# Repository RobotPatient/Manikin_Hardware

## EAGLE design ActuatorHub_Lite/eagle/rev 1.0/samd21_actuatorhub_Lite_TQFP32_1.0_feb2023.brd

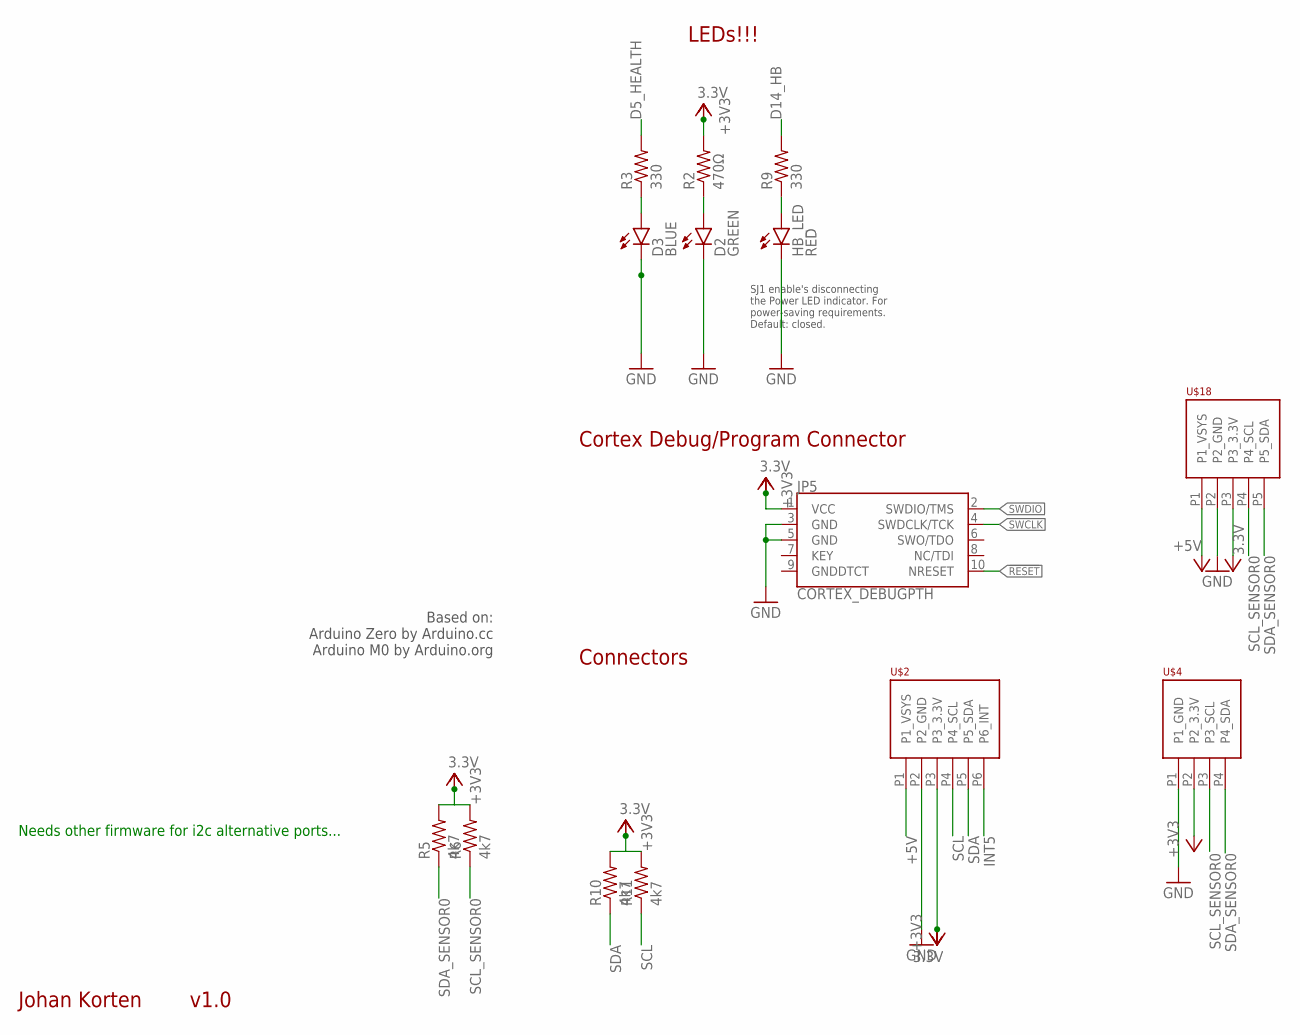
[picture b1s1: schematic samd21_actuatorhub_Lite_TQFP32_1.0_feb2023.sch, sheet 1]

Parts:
D2: GREEN; LED-0603
D3: BLUE; LED-0603
HB_LED: RED; LED-0603
JP5: CORTEX_DEBUGPTH; 2X5-PTH-1.27MM
R2: 470Ω; 0603-RES
R3, R9: 330; 0603-RES
R5, R6, R10, R11: 4k7; 0603-RES
U$2: PHOENIX_PTSM_M6_TH_I2CPPANGLE; PTSM_M6_THRHOLE
U$4: PHOENIX_PTSM_M4_THANGLE; PTSM_M4_TH
U$18: PHOENIX_PTSM_M5_TH_I2C++; PTSM_M5_THRHOLE

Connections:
3.3V: JP5.1 (VCC), R2.2, R5.2, R6.2, R10.2, R11.2, U$2.P3 (P3_3.3V), U$4.P2 (P2_3.3V), U$18.P3 (P3_3.3V); also elsewhere on the board
!RESET: JP5.10 (NRESET); also elsewhere on the board
+5V: U$2.P1 (P1_VSYS), U$18.P1 (P1_VSYS); also elsewhere on the board
D5_HEALTH: R3.2; also elsewhere on the board
D5_HEALTH_LED: D3.A, R3.1
D14_HB: R9.2; also elsewhere on the board
D14_HB_LED: HB_LED.A, R9.1
GND: D2.C, D3.C, HB_LED.C, JP5.3 (GND), JP5.5 (GND), U$2.P2 (P2_GND), U$4.P1 (P1_GND), U$18.P2 (P2_GND); also elsewhere on the board
INT5: U$2.P6 (P6_INT); also elsewhere on the board
unnamed: D2.A, R2.1
SCL: R11.1, U$2.P4 (P4_SCL); also elsewhere on the board
SCL_SENSOR0: R6.1, U$4.P3 (P3_SCL), U$18.P4 (P4_SCL); also elsewhere on the board
SDA: R10.1, U$2.P5 (P5_SDA); also elsewhere on the board
SDA_SENSOR0: R5.1, U$4.P4 (P4_SDA), U$18.P5 (P5_SDA); also elsewhere on the board
SWCLK: JP5.4 (SWDCLK/TCK); also elsewhere on the board
SWDIO: JP5.2 (SWDIO/TMS); also elsewhere on the board

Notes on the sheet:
LEDs!!!
Cortex Debug/Program Connector
Connectors
Johan Korten
v1.0
SJ1 enable's disconnecting the Power LED indicator. For power-saving requirements. Default: closed.
Based on: Arduino Zero by Arduino.cc Arduino M0 by Arduino.org
Needs other firmware for i2c alternative ports...

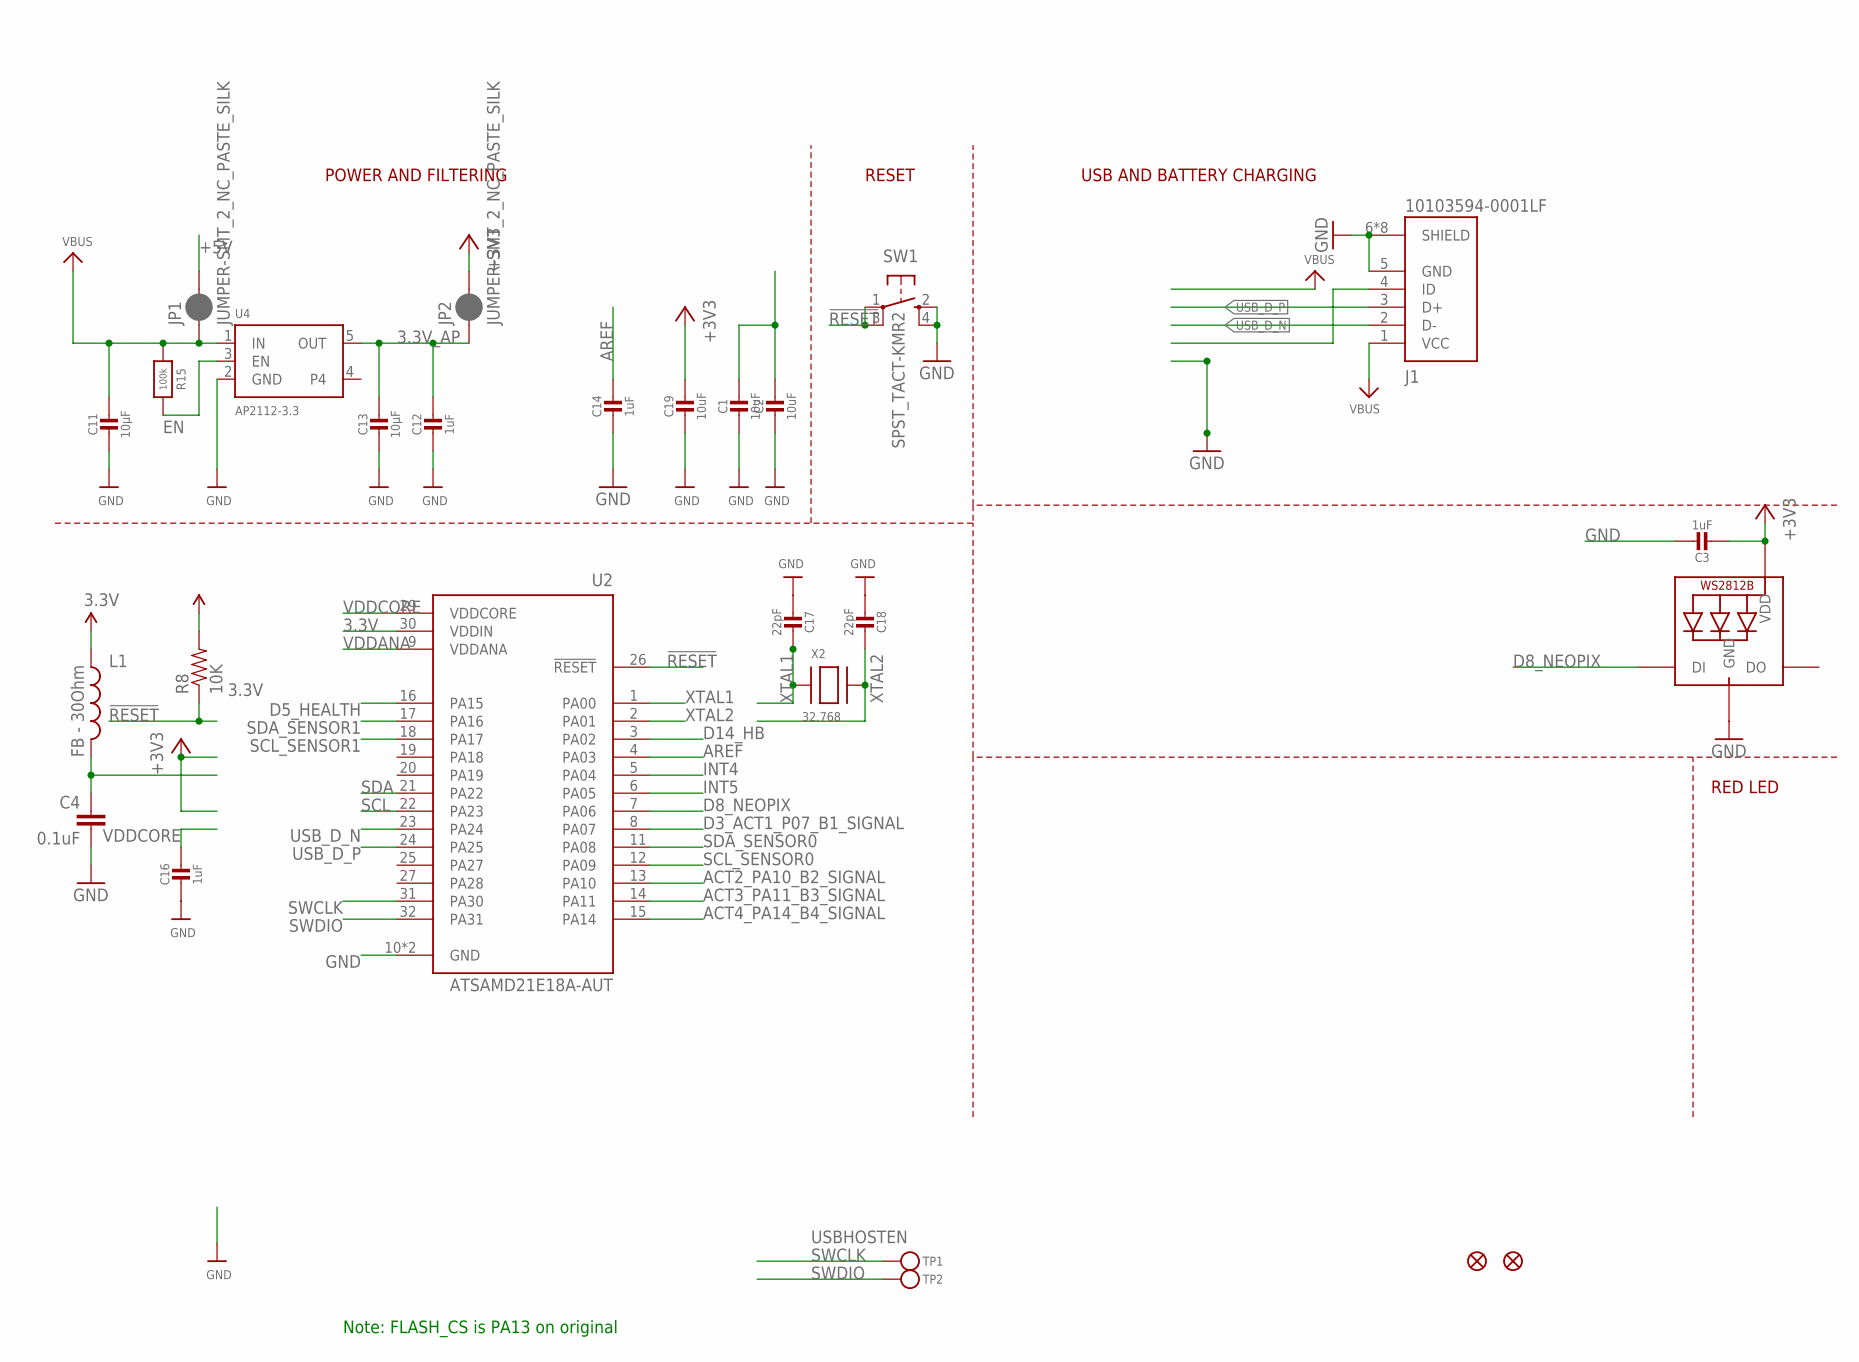
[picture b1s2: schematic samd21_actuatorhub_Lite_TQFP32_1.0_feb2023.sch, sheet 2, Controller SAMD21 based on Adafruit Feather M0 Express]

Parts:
C1, C2, C19: 10uF; 0805-NO
C3, C12, C14, C16: 1uF; 0603-NO
C4: 0.1uF; 0402-CAP
C11, C13: 10µF; 0805-NO
C17, C18: 22pF; 0603-NO
J1: 10103594-0001LF; AMPHENOL_10103594-0001LF
JP1, JP2: JUMPER-SMT_2_NC_PASTE_SILK; SMT-JUMPER_2_NC_PASTE_SILK
L1: FB - 30Ohm; 0603
LED1: WS2812B3535; LED3535
R8: 10K; 0603-RES
R15: 100k; 0603-NO
SW1: SPST_TACT-KMR2; KMR2
TP1, TP2: TESTPOINTROUND1.5MM; TESTPOINT_ROUND_1.5MM
U2: ATSAMD21E18A-AUT; QFP80P900X900X120-32N
U4: AP2112-3.3; SOT23-5
U$34, U$35: FIDUCIAL""; FIDUCIAL_1MM
X2: 32.768; XTAL3215

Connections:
3.3V: C3.2, C19.1, JP2.2, L1.1, LED1.2 (VDD), R8.2, U2.30 (VDDIN); also elsewhere on the board
3.3V_AP: C12.1, C13.1, JP2.1, U4.5 (OUT)
!RESET: R8.1, SW1.1, SW1.3 (P1), U2.26 (!RESET); also elsewhere on the board
+5V: C1.1, C2.1, JP1.2; also elsewhere on the board
ACT2_PA10_B2_SIGNAL: U2.13 (PA10); also elsewhere on the board
ACT3_PA11_B3_SIGNAL: U2.14 (PA11); also elsewhere on the board
ACT4_PA14_B4_SIGNAL: U2.15 (PA14); also elsewhere on the board
AREF: C14.1, U2.4 (PA03)
D3_ACT1_P07_B1_SIGNAL: U2.8 (PA07); also elsewhere on the board
D5_HEALTH: U2.16 (PA15); also elsewhere on the board
D8_NEOPIX: LED1.1 (DI), U2.7 (PA06)
D14_HB: U2.3 (PA02); also elsewhere on the board
EN: R15.2, U4.3 (EN)
GND: C1.2, C2.2, C3.1, C4.2, C11.2, C12.2, C13.2, C14.2, C16.2, C17.2, C18.2, C19.2, J1.5 (GND), J1.6 (SHIELD), J1.7 (SHIELD), J1.8 (SHIELD), J1.9 (SHIELD), J1.10 (SHIELD), J1.11 (SHIELD), J1.S1 (SHIELD), J1.S2 (SHIELD), LED1.4 (GND), SW1.2 (S), SW1.4 (S1), U2.10 (GND), U2.28 (GND), U4.2 (GND); also elsewhere on the board
INT4: U2.5 (PA04)
INT5: U2.6 (PA05); also elsewhere on the board
SCL: U2.22 (PA23); also elsewhere on the board
SCL_SENSOR0: U2.12 (PA09); also elsewhere on the board
SCL_SENSOR1: U2.18 (PA17)
SDA: U2.21 (PA22); also elsewhere on the board
SDA_SENSOR0: U2.11 (PA08); also elsewhere on the board
SDA_SENSOR1: U2.17 (PA16)
SWCLK: TP1.P$1, U2.31 (PA30); also elsewhere on the board
SWDIO: TP2.P$1, U2.32 (PA31); also elsewhere on the board
USB_D_N: J1.2 (D-), U2.23 (PA24)
USB_D_P: J1.3 (D+), U2.24 (PA25)
VBUS: C11.1, J1.1 (VCC), JP1.1, R15.1, U4.1 (IN)
VDDANA: C4.1, L1.2, U2.9 (VDDANA)
VDDCORE: C16.1, U2.29 (VDDCORE)
XTAL1: C17.1, U2.1 (PA00), X2.P$1
XTAL2: C18.1, U2.2 (PA01), X2.P$2

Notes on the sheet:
POWER AND FILTERING
RESET
USBHOSTEN
USB AND BATTERY CHARGING
RED LED
Note: FLASH_CS is PA13 on original

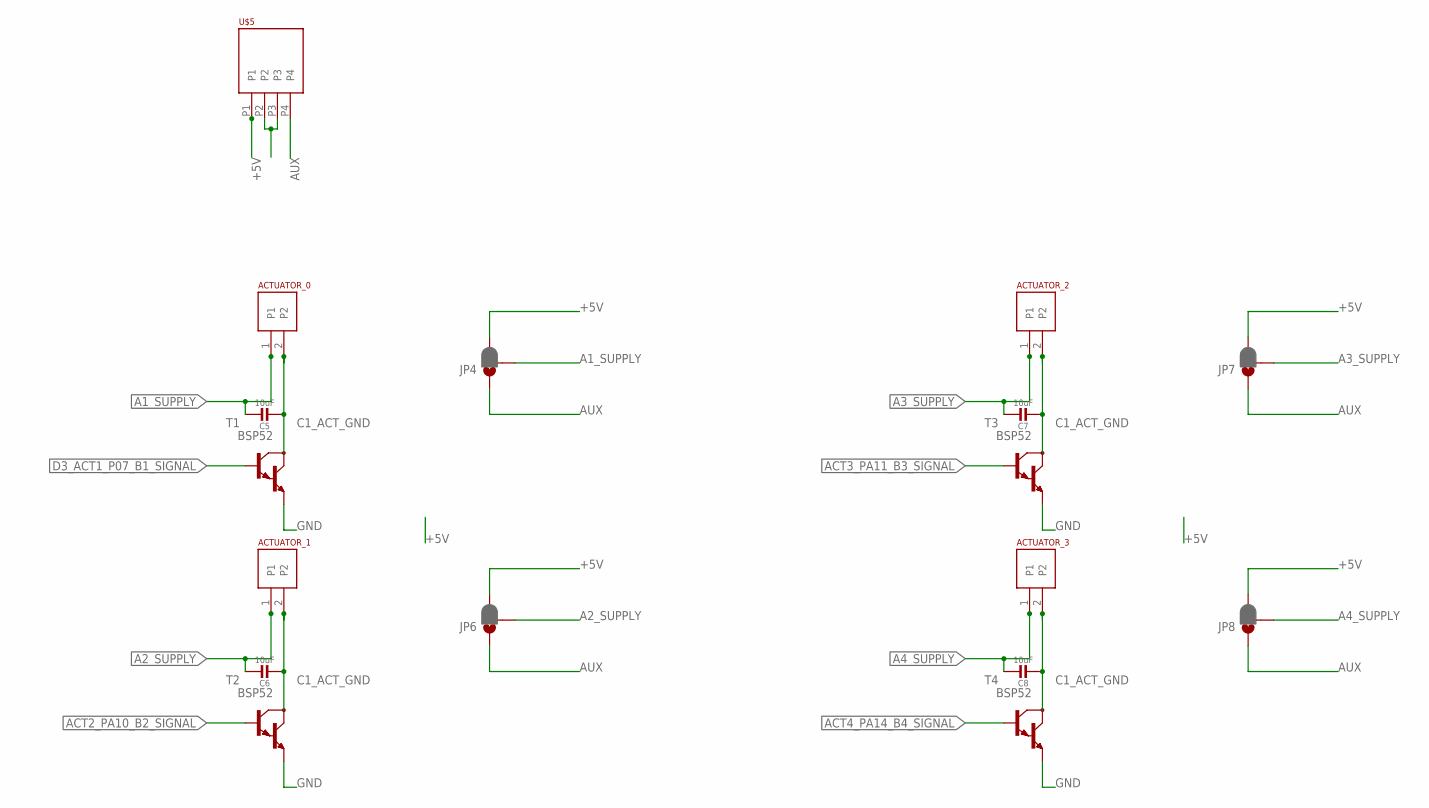
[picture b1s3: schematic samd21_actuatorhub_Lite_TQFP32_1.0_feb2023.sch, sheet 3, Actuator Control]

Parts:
ACTUATOR_0, ACTUATOR_1, ACTUATOR_2, ACTUATOR_3: PHOENIX_PTSM_M2TH; PTSM_M2_THRHOLE
C5, C6, C7, C8: 10uF; 0805-NO
JP4, JP6, JP7, JP8: JUMPER-SMT_3_1-NC_PASTE_SILK; SMT-JUMPER_3_1-NC_PASTE_SILK
T1, T2, T3, T4: BSP52; SOT-223-4
U$5: PHOENIX_PTSM_M4_TH_ANGLE; PTSM_M4_TH_ANGLE_NEUTRAL

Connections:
+5V: JP4.3, JP6.3, JP7.3, JP8.3, U$5.P1; also elsewhere on the board
A1_SUPPLY: ACTUATOR_0.1, C5.1, JP4.2
A2_SUPPLY: ACTUATOR_1.1, C6.1, JP6.2
A3_SUPPLY: ACTUATOR_2.1, C7.1, JP7.2
A4_SUPPLY: ACTUATOR_3.1, C8.1, JP8.2
ACT2_PA10_B2_SIGNAL: T2.1 (B); also elsewhere on the board
ACT3_PA11_B3_SIGNAL: T3.1 (B); also elsewhere on the board
ACT4_PA14_B4_SIGNAL: T4.1 (B); also elsewhere on the board
AUX: JP4.1, JP6.1, JP7.1, JP8.1, U$5.P4
C1_ACT_GND: ACTUATOR_0.2, ACTUATOR_1.2, ACTUATOR_2.2, ACTUATOR_3.2, C5.2, C6.2, C7.2, C8.2, T1.2 (C), T1.4 (C), T2.2 (C), T2.4 (C), T3.2 (C), T3.4 (C), T4.2 (C), T4.4 (C)
D3_ACT1_P07_B1_SIGNAL: T1.1 (B); also elsewhere on the board
GND: T1.3 (E), T2.3 (E), T3.3 (E), T4.3 (E); also elsewhere on the board
unnamed: U$5.P2, U$5.P3

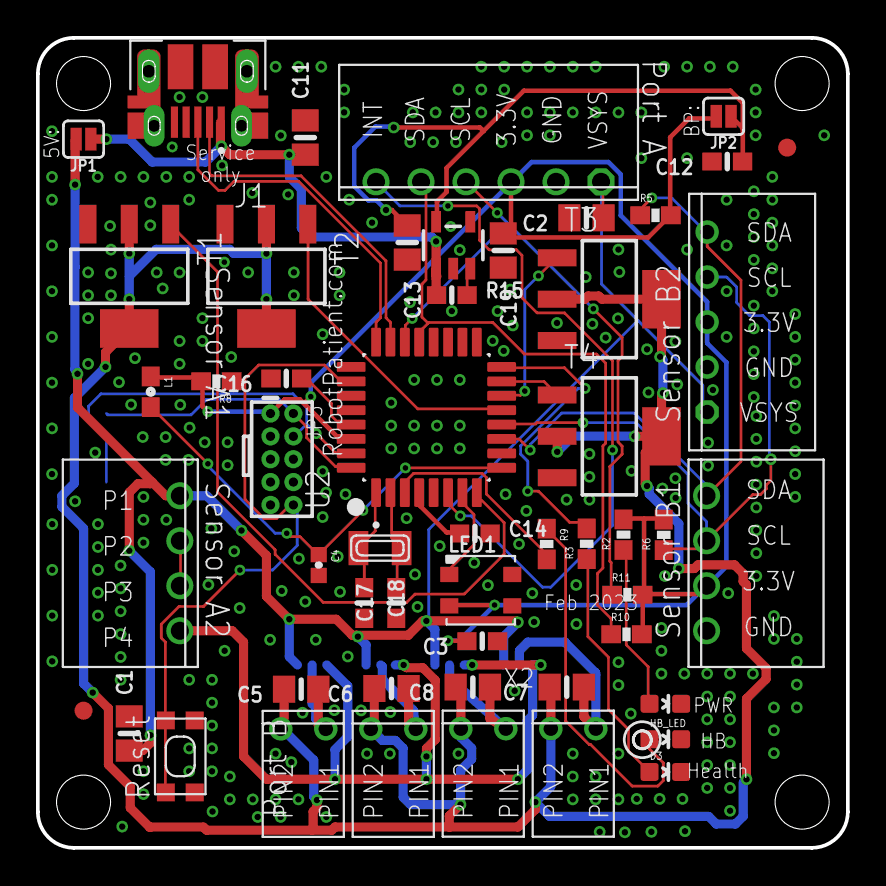
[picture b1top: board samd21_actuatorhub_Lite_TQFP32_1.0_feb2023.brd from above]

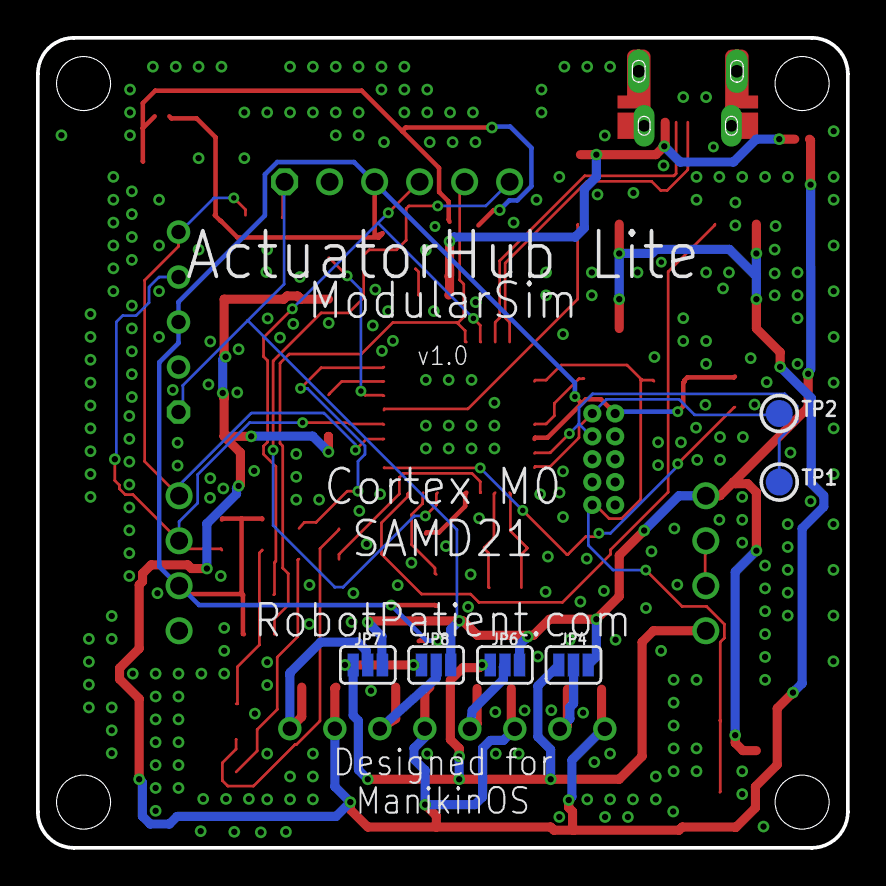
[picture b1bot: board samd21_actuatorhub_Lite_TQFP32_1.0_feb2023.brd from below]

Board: 2 copper layers, 45.0 x 45.0 mm, 58 parts (6 on the bottom side), 38 nets.

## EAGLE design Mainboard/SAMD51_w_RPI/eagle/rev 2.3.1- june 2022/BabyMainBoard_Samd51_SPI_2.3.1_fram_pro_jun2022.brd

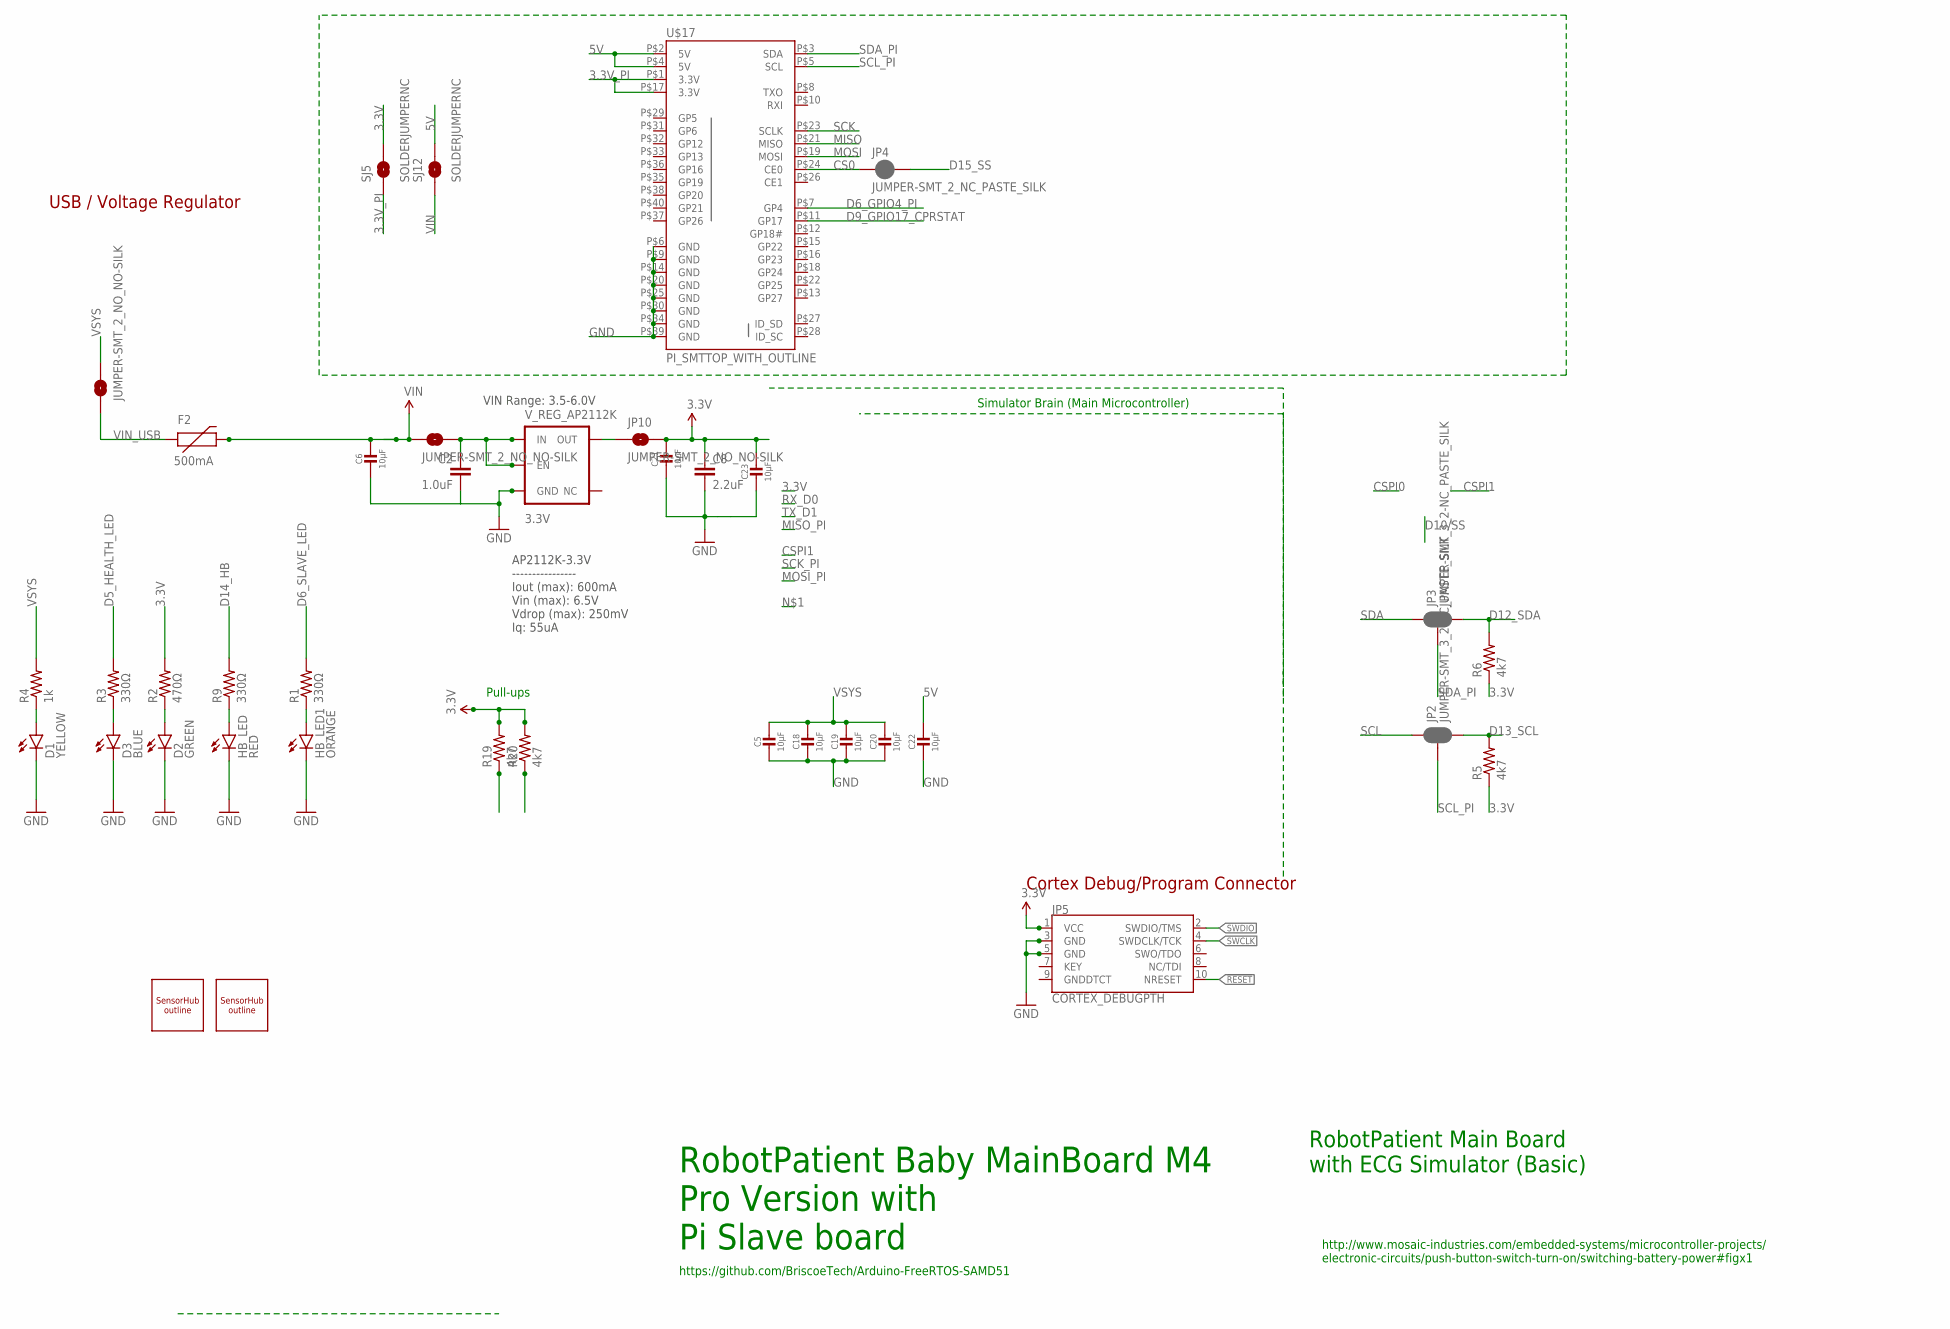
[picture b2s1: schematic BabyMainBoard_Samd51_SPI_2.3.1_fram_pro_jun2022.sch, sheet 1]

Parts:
C2: 1.0uF; 0805-CAP
C5, C6, C18, C19, C20, C21, C22, C23: 10µF; 0805
C8: 2.2uF; 0603-CAP
D1: YELLOW; LED-0603
D2: GREEN; LED-0603
D3: BLUE; LED-0603
F2: 500mA; PTC-1206
HB_LED: RED; LED-0603
HB_LED1: ORANGE; LED-0603
JP1, JP10, JP11: JUMPER-SMT_2_NO_NO-SILK; SMT-JUMPER_2_NO_NO-SILK
JP2, JP3: JUMPER-SMT_3_2-NC_PASTE_SILK; SMT-JUMPER_3_2-NC_PASTE_SILK
JP4: JUMPER-SMT_2_NC_PASTE_SILK; SMT-JUMPER_2_NC_PASTE_SILK
JP5: CORTEX_DEBUGPTH; 2X5-PTH-1.27MM
R1, R3, R9: 330Ω; 0603-RES
R2: 470Ω; 0603-RES
R4: 1k; 0603-RES
R5, R6, R19, R20: 4k7; 0603-RES
SJ5, SJ12: SOLDERJUMPERNC; SJ_2S
U$15, U$16: SENSORHUB_PROFILEOUTLINE; SENSORHUB_HOLES
U$17: PI_SMTTOP_WITH_OUTLINE; PI_SMT_ZERO
V_REG_AP2112K: 3.3V; SOT23-5

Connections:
3.3V: C8.1, C21.1, C23.1, JP5.1 (VCC), JP10.2, R2.2, R5.1, R6.1, R19.2, R20.2, SJ5.2; also elsewhere on the board
3.3V_IN: C2.1, JP11.2, V_REG_AP2112K.1 (IN), V_REG_AP2112K.3 (EN)
3.3V_PI: SJ5.1, U$17.P$1 (3.3V), U$17.P$17 (3.3V)
3V3_LED: D2.A, R2.1
5V: C22.1, SJ12.2, U$17.P$2 (5V), U$17.P$4 (5V); also elsewhere on the board
5V_LED: D1.A, R4.1
!RESET: JP5.10 (NRESET); also elsewhere on the board
CS0: JP4.1, U$17.P$24 (CE0)
D5_HEALTH_LED: D3.A, R3.1, R3.2; also elsewhere on the board
D6_GPIO4_PI: U$17.P$7 (GP4)
D6_SLAVE_LED: R1.2; also elsewhere on the board
D6_SLAVE_LED1: HB_LED1.A, R1.1
D9_GPIO17_CPRSTAT: U$17.P$11 (GP17); also elsewhere on the board
D12_SDA: JP3.3, R6.2; also elsewhere on the board
D13_SCL: JP2.3, R5.2; also elsewhere on the board
D14_HB: R9.2; also elsewhere on the board
D14_HB_LED: HB_LED.A, R9.1
D15_SS: JP4.2; also elsewhere on the board
GND: C2.2, C5.2, C6.2, C8.2, C18.2, C19.2, C20.2, C21.2, C22.2, C23.2, D1.C, D2.C, D3.C, HB_LED.C, HB_LED1.C, JP5.3 (GND), JP5.5 (GND), U$17.P$6 (GND), U$17.P$9 (GND), U$17.P$14 (GND), U$17.P$20 (GND), U$17.P$25 (GND), U$17.P$30 (GND), U$17.P$34 (GND), U$17.P$39 (GND), V_REG_AP2112K.2 (GND); also elsewhere on the board
MISO: U$17.P$21 (MISO); also elsewhere on the board
MOSI: U$17.P$19 (MOSI); also elsewhere on the board
unnamed: JP10.1, V_REG_AP2112K.5 (OUT)
SCK: U$17.P$23 (SCLK); also elsewhere on the board
SCL: JP2.1, R19.1; also elsewhere on the board
SCL_PI: JP2.2, U$17.P$5 (SCL)
SDA: JP3.1, R20.1; also elsewhere on the board
SDA_PI: JP3.2, U$17.P$3 (SDA)
SWCLK: JP5.4 (SWDCLK/TCK); also elsewhere on the board
SWDIO: JP5.2 (SWDIO/TMS); also elsewhere on the board
VIN: C6.1, F2.2, JP11.1, SJ12.1
VIN_USB: F2.1, JP1.1; also elsewhere on the board
VSYS: C5.1, C18.1, C19.1, C20.1, JP1.2, R4.2; also elsewhere on the board

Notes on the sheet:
RobotPatient Main Board with ECG Simulator (Basic)
Simulator Brain (Main Microcontroller)
http://www.mosaic-industries.com/embedded-systems/microcontroller-projects/ electronic-circuits/push-button-switch-turn-on/switching-battery-power#figx1
RobotPatient Baby MainBoard M4 Pro Version with Pi Slave board
VIN Range: 3.5-6.0V
AP2112K-3.3V ---------------- Iout (max): 600mA Vin (max): 6.5V Vdrop (max): 250mV Iq: 55uA
Pull-ups
Cortex Debug/Program Connector
USB / Voltage Regulator
https://github.com/BriscoeTech/Arduino-FreeRTOS-SAMD51

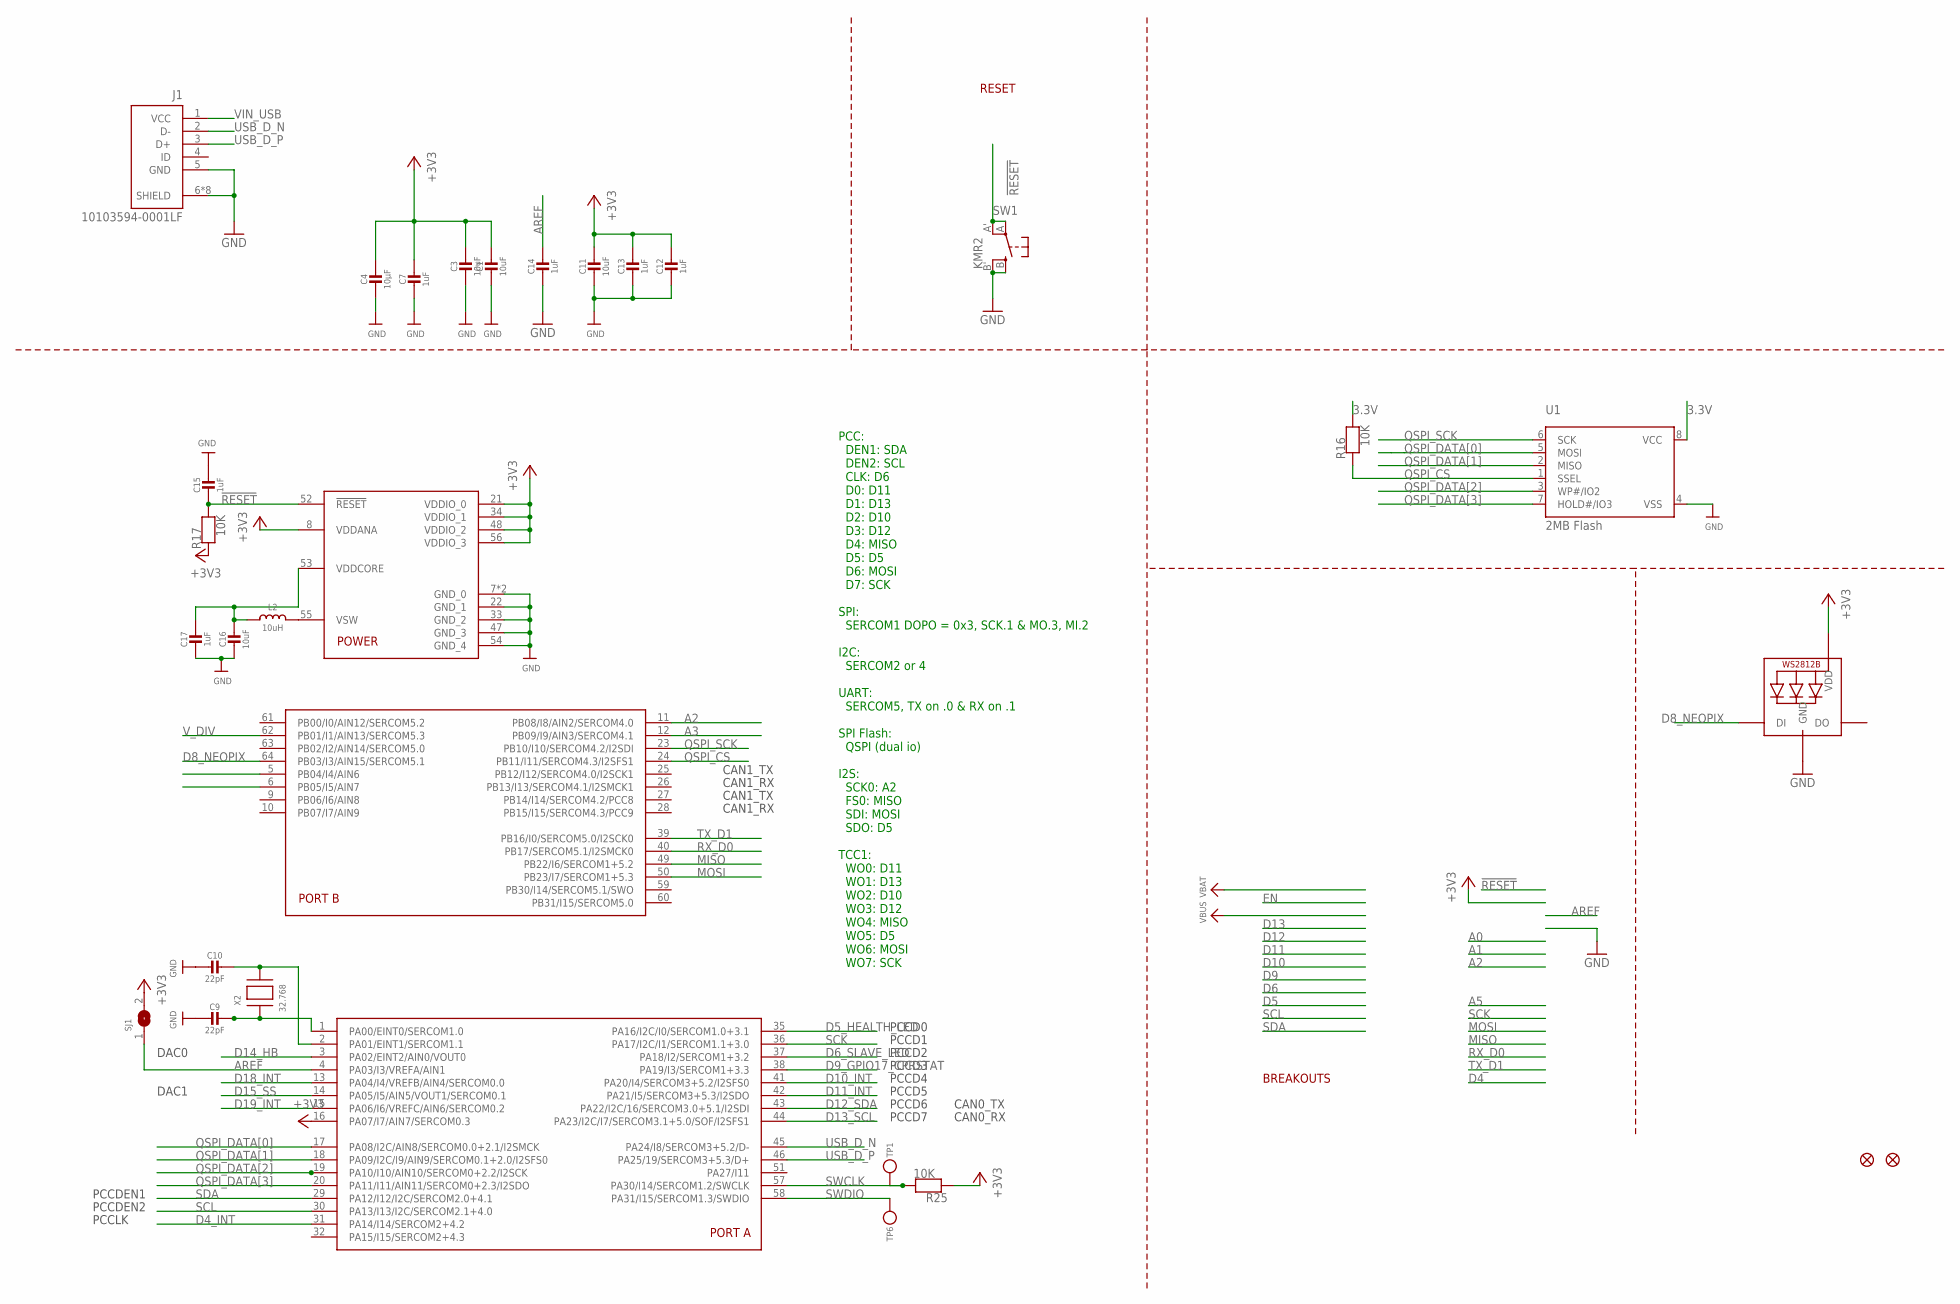
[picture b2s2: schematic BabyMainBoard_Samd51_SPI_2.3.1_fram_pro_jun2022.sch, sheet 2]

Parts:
C1, C3, C11, C16: 10uF; 0805
C4: 10µF; 0805
C7, C12, C13, C14, C15, C17: 1uF; 0603
C9, C10: 22pF; 0603
J1: 10103594-0001LF; AMPHENOL_10103594-0001LF
L2: 10uH; INDUCTOR_1007
LED3: WS2812B3535; LED3535
R16, R17, R25: 10K; 0603
SJ1: SOLDERJUMPERCLOSED; SOLDERJUMPER_CLOSEDWIRE
SW1: KMR2; BTN_KMR2_4.6X2.8
TP1, TP6: TESTPOINTROUND1MM; TESTPOINT_ROUND_1MM
U1: 2MB Flash; USON8
U$14: ATSAMD51J; PQFN64-1
U$34, U$35: FIDUCIAL""; FIDUCIAL_1MM
X2: 32.768; XTAL3215

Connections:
3.3V: C1.1, C3.1, C4.1, C7.1, C11.1, C12.1, C13.1, LED3.2 (VDD), R16.2, R17.1, R25.1, SJ1.2, U1.8 (VCC), U$14.8 (VDDANA), U$14.16 (PA07/I7/AIN7/SERCOM0.3), U$14.21 (VDDIO_0), U$14.34 (VDDIO_1), U$14.48 (VDDIO_2), U$14.56 (VDDIO_3); also elsewhere on the board
!RESET: C15.2, R17.2, SW1.A, SW1.A' (P1), U$14.52 (!RESET); also elsewhere on the board
A2: U$14.11 (PB08/I8/AIN2/SERCOM4.0)
A3: U$14.12 (PB09/I9/AIN3/SERCOM4.1)
AREF: C14.1, SJ1.1, U$14.4 (PA03/I3/VREFA/AIN1)
D4_INT: U$14.31 (PA14/I14/SERCOM2+4.2); also elsewhere on the board
D5_HEALTH_LED: U$14.35 (PA16/I2C/I0/SERCOM1.0+3.1); also elsewhere on the board
D6_SLAVE_LED: U$14.37 (PA18/I2/SERCOM1+3.2); also elsewhere on the board
D8_NEOPIX: LED3.1 (DI), U$14.64 (PB03/I3/AIN15/SERCOM5.1)
D9_GPIO17_CPRSTAT: U$14.38 (PA19/I3/SERCOM1+3.3); also elsewhere on the board
D10_INT: U$14.41 (PA20/I4/SERCOM3+5.2/I2SFS0); also elsewhere on the board
D11_INT: U$14.42 (PA21/I5/SERCOM3+5.3/I2SDO); also elsewhere on the board
D12_SDA: U$14.43 (PA22/I2C/16/SERCOM3.0+5.1/I2SDI); also elsewhere on the board
D13_SCL: U$14.44 (PA23/I2C/I7/SERCOM3.1+5.0/SOF/I2SFS1); also elsewhere on the board
D14_HB: U$14.3 (PA02/EINT2/AIN0/VOUT0); also elsewhere on the board
D15_SS: U$14.14 (PA05/I5/AIN5/VOUT1/SERCOM0.1); also elsewhere on the board
D18_INT: U$14.13 (PA04/I4/VREFB/AIN4/SERCOM0.0); also elsewhere on the board
D19_INT: U$14.15 (PA06/I6/VREFC/AIN6/SERCOM0.2); also elsewhere on the board
GND: C1.2, C3.2, C4.2, C7.2, C9.2, C10.2, C11.2, C12.2, C13.2, C14.2, C15.1, C16.2, C17.2, J1.5 (GND), J1.6 (SHIELD), J1.7 (SHIELD), J1.8 (SHIELD), J1.9 (SHIELD), J1.10 (SHIELD), J1.11 (SHIELD), J1.S1 (SHIELD), J1.S2 (SHIELD), LED3.4 (GND), SW1.B (S), SW1.B' (S1), U1.4 (VSS), U$14.7 (GND_0), U$14.22 (GND_1), U$14.33 (GND_2), U$14.47 (GND_3), U$14.54 (GND_4), U$14.EXP (GND_0); also elsewhere on the board
MISO: U$14.49 (PB22/I6/SERCOM1+5.2); also elsewhere on the board
MOSI: U$14.50 (PB23/I7/SERCOM1+5.3); also elsewhere on the board
unnamed: C9.1, U$14.1 (PA00/EINT0/SERCOM1.0), X2.P$1
unnamed: C10.1, U$14.2 (PA01/EINT1/SERCOM1.1), X2.P$2
unnamed: L2.P$2 (2), U$14.55 (VSW)
QSPI_CS: R16.1, U1.1 (SSEL), U$14.24 (PB11/I11/SERCOM4.3/I2SFS1)
QSPI_DATA[0]: U1.5 (MOSI), U$14.17 (PA08/I2C/AIN8/SERCOM0.0+2.1/I2SMCK)
QSPI_DATA[1]: U1.2 (MISO), U$14.18 (PA09/I2C/I9/AIN9/SERCOM0.1+2.0/I2SFS0)
QSPI_DATA[2]: U1.3 (WP#/IO2), U$14.19 (PA10/I10/AIN10/SERCOM0+2.2/I2SCK)
QSPI_DATA[3]: U1.7 (HOLD#/IO3), U$14.20 (PA11/I11/AIN11/SERCOM0+2.3/I2SDO)
QSPI_SCK: U1.6 (SCK), U$14.23 (PB10/I10/SERCOM4.2/I2SDI)
RX_D0: U$14.40 (PB17/SERCOM5.1/I2SMCK0); also elsewhere on the board
SCK: U$14.36 (PA17/I2C/I1/SERCOM1.1+3.0); also elsewhere on the board
SCL: U$14.30 (PA13/I13/I2C/SERCOM2.1+4.0); also elsewhere on the board
SDA: U$14.29 (PA12/I12/I2C/SERCOM2.0+4.1); also elsewhere on the board
SWCLK: R25.2, TP1.P$1, U$14.57 (PA30/I14/SERCOM1.2/SWCLK); also elsewhere on the board
SWDIO: TP6.P$1, U$14.58 (PA31/I15/SERCOM1.3/SWDIO); also elsewhere on the board
TX_D1: U$14.39 (PB16/I0/SERCOM5.0/I2SCK0); also elsewhere on the board
USB_D_N: J1.2 (D-), U$14.45 (PA24/I8/SERCOM3+5.2/D-)
USB_D_P: J1.3 (D+), U$14.46 (PA25/19/SERCOM3+5.3/D+)
VDDCORE1: C16.1, C17.1, L2.P$1 (1), U$14.53 (VDDCORE)
VIN_USB: J1.1 (VCC); also elsewhere on the board
V_DIV: U$14.62 (PB01/I1/AIN13/SERCOM5.3)

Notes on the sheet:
RESET
BREAKOUTS
PCCDEN1
PCCDEN2
PCCD0
PCCD1
PCCD2
PCCD3
PCCD4
PCCD5
PCCD6
PCCD7
PCCLK
PCC: DEN1: SDA DEN2: SCL CLK: D6 D0: D11 D1: D13 D2: D10 D3: D12 D4: MISO D5: D5 D6: MOSI D7: SCK SPI: SERCOM1 DOPO = 0x3, SCK.1 & MO.3, MI.2 I2C: SERCOM2 or 4 UART: SERCOM5, TX on .0 & RX on .1 SPI Flash: QSPI (dual io) I2S: SCK0: A2 FS0: MISO SDI: MOSI SDO: D5 TCC1: WO0: D11 WO1: D13 WO2: D10 WO3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
CAN0_TX
CAN0_RX
DAC0
DAC1
CAN1_TX
CAN1_RX

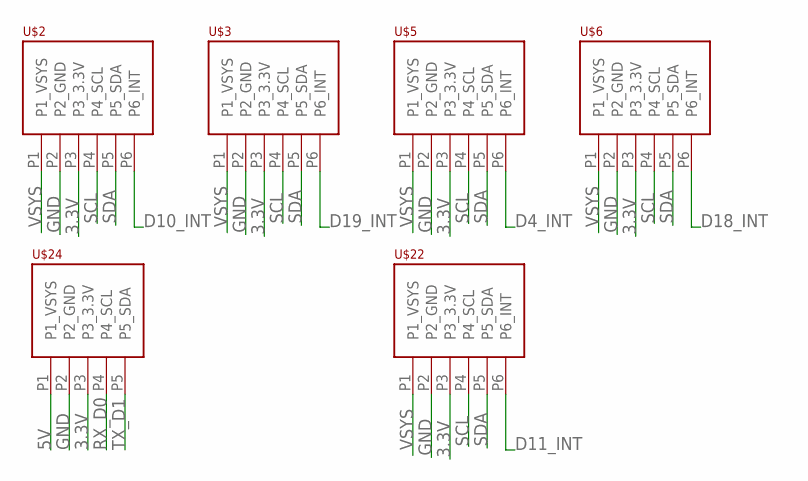
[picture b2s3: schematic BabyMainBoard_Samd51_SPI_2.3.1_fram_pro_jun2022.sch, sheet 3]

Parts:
U$2, U$3, U$5, U$22: PHOENIX_PTSM_M6_TH_I2CPPANGLE; PTSM_M6_THRHOLE
U$6: PHOENIX_PTSM_M6_TH_I2CPPSTRAIGHT; PTSM_M6_TH_UP_NEUTRAL
U$24: PHOENIX_PTSM_M5_THUART; PTSM_M5_TH_UART

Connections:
3.3V: U$2.P3 (P3_3.3V), U$3.P3 (P3_3.3V), U$5.P3 (P3_3.3V), U$6.P3 (P3_3.3V), U$22.P3 (P3_3.3V), U$24.P3 (P3_3.3V); also elsewhere on the board
5V: U$24.P1 (P1_VSYS); also elsewhere on the board
D4_INT: U$5.P6 (P6_INT); also elsewhere on the board
D10_INT: U$2.P6 (P6_INT); also elsewhere on the board
D11_INT: U$22.P6 (P6_INT); also elsewhere on the board
D18_INT: U$6.P6 (P6_INT); also elsewhere on the board
D19_INT: U$3.P6 (P6_INT); also elsewhere on the board
GND: U$2.P2 (P2_GND), U$3.P2 (P2_GND), U$5.P2 (P2_GND), U$6.P2 (P2_GND), U$22.P2 (P2_GND), U$24.P2 (P2_GND); also elsewhere on the board
RX_D0: U$24.P4 (P4_SCL); also elsewhere on the board
SCL: U$2.P4 (P4_SCL), U$3.P4 (P4_SCL), U$5.P4 (P4_SCL), U$6.P4 (P4_SCL), U$22.P4 (P4_SCL); also elsewhere on the board
SDA: U$2.P5 (P5_SDA), U$3.P5 (P5_SDA), U$5.P5 (P5_SDA), U$6.P5 (P5_SDA), U$22.P5 (P5_SDA); also elsewhere on the board
TX_D1: U$24.P5 (P5_SDA); also elsewhere on the board
VSYS: U$2.P1 (P1_VSYS), U$3.P1 (P1_VSYS), U$5.P1 (P1_VSYS), U$6.P1 (P1_VSYS), U$22.P1 (P1_VSYS); also elsewhere on the board

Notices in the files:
parts and their libraries:
SparkFun-Resistors: Licensing: Creative Commons ShareAlike 4.0 International - https://creativecommons.org/licenses/by-sa/4.0
microbuilder: This work is placed in the public domain, and may be freely used for commercial and non-commercial work with the following conditions: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
